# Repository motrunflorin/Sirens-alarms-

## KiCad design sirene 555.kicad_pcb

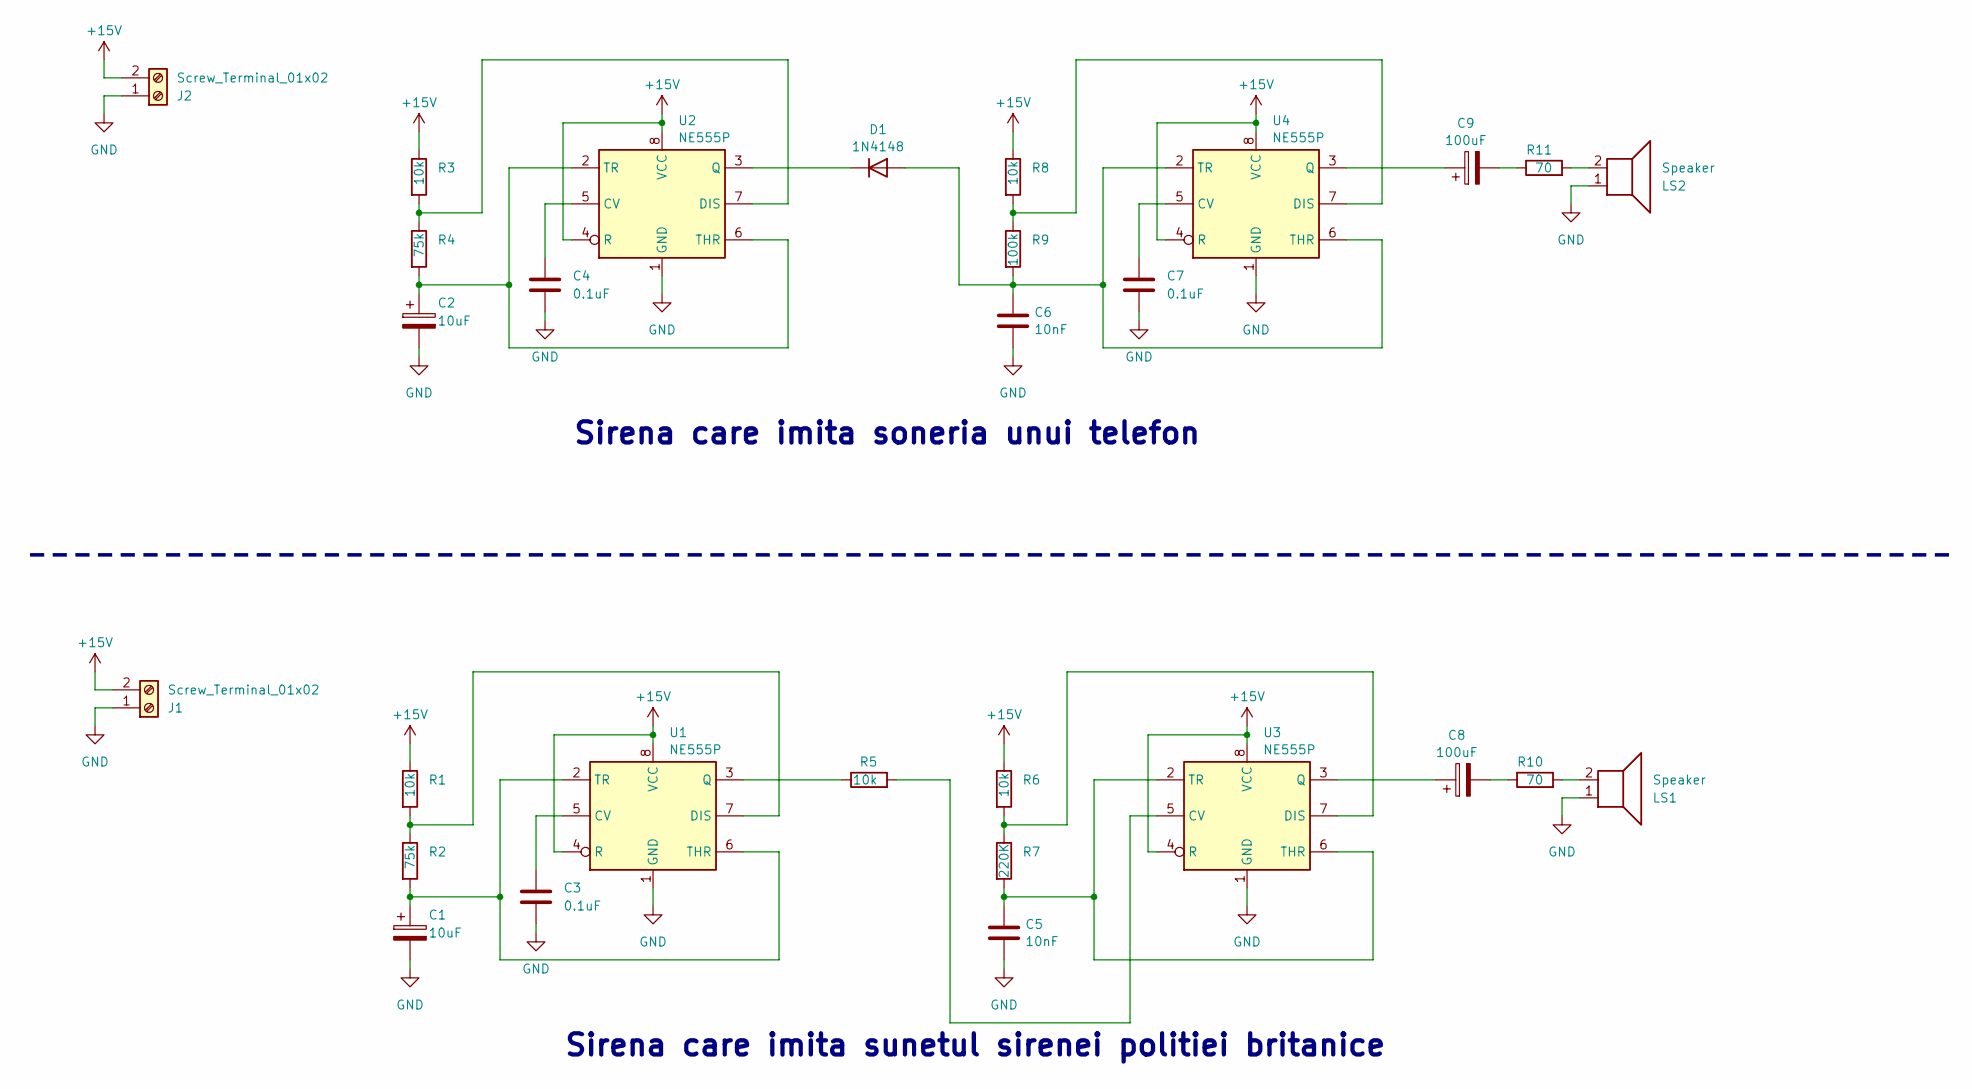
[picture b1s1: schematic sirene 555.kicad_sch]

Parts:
C1, C2: 10uF; CP_Radial_D5.0mm_P2.50mm
C3, C4, C7: 0.1uF; C_Disc_D4.3mm_W1.9mm_P5.00mm
C5, C6: 10nF; C_Disc_D4.3mm_W1.9mm_P5.00mm
C8, C9: 100uF; CP_Radial_D6.3mm_P2.50mm
D1: 1N4148; D_DO-35_SOD27_P7.62mm_Horizontal
J1, J2: Screw_Terminal_01x02; PhoenixContact_MSTBA_2,5_2-G_1x02_P5.00mm_Horizontal
LS1, LS2: Speaker; PhoenixContact_MSTBA_2,5_2-G_1x02_P5.00mm_Horizontal
R1, R3, R5, R6, R8: 10k; R_Axial_DIN0207_L6.3mm_D2.5mm_P7.62mm_Horizontal; Mfr.Part. MBB02070C1002DC100
R2, R4: 75k; R_Axial_DIN0207_L6.3mm_D2.5mm_P7.62mm_Horizontal
R7: 220K; R_Axial_DIN0207_L6.3mm_D2.5mm_P7.62mm_Horizontal
R9: 100k; R_Axial_DIN0207_L6.3mm_D2.5mm_P7.62mm_Horizontal
R10, R11: 70; R_Axial_DIN0207_L6.3mm_D2.5mm_P7.62mm_Horizontal
U1, U2, U3, U4: NE555P; DIP-8_W7.62mm

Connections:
+15V: J1.2, J2.2, R1.1, R3.1, R6.1, R8.1, U1.4 (R), U1.8 (VCC), U2.4 (R), U2.8 (VCC), U3.4 (R), U3.8 (VCC), U4.4 (R), U4.8 (VCC)
GND: C1.2, C2.2, C3.2, C4.2, C5.2, C6.2, C7.2, J1.1, J2.1, LS1.1, LS2.1, U1.1 (GND), U2.1 (GND), U3.1 (GND), U4.1 (GND)
unnamed: C8.2, R10.1
unnamed: C9.2, R11.1
unnamed: C6.1, D1.2 (A), R9.2, U4.2 (TR), U4.6 (THR)
unnamed: D1.1 (K), U2.3 (Q)
unnamed: LS1.2, R10.2
unnamed: LS2.2, R11.2
unnamed: C3.1, U1.5 (CV)
unnamed: R1.2, R2.1, U1.7 (DIS)
unnamed: R5.1, U1.3 (Q)
unnamed: C1.1, R2.2, U1.2 (TR), U1.6 (THR)
unnamed: C4.1, U2.5 (CV)
unnamed: R3.2, R4.1, U2.7 (DIS)
unnamed: C2.1, R4.2, U2.2 (TR), U2.6 (THR)
unnamed: R5.2, U3.5 (CV)
unnamed: R6.2, R7.1, U3.7 (DIS)
unnamed: C8.1, U3.3 (Q)
unnamed: C5.1, R7.2, U3.2 (TR), U3.6 (THR)
unnamed: C7.1, U4.5 (CV)
unnamed: R8.2, R9.1, U4.7 (DIS)
unnamed: C9.1, U4.3 (Q)

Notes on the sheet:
Sirena care imita sunetul sirenei politiei britanice
Sirena care imita soneria unui telefon

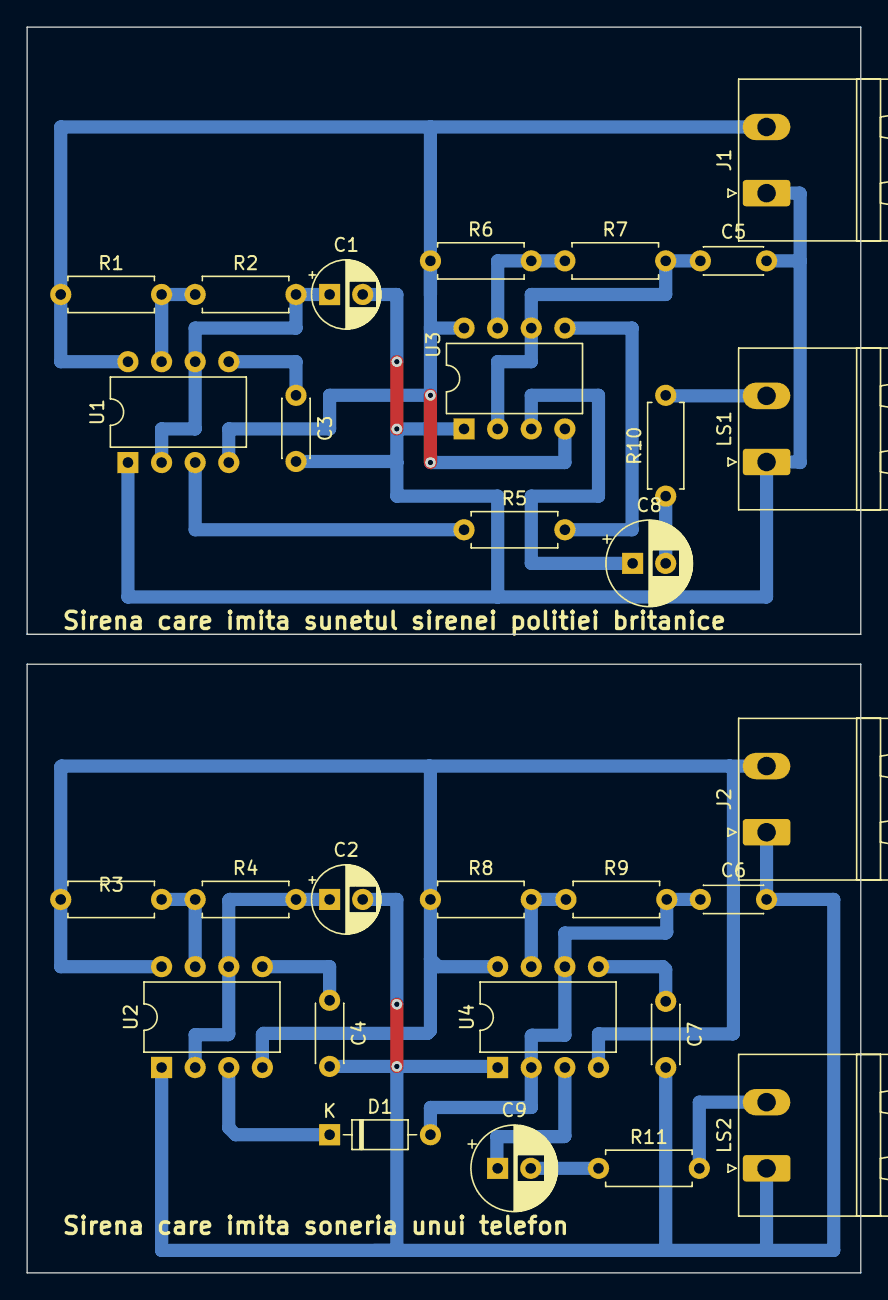
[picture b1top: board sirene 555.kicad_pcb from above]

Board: 2 copper layers, 63.0 x 94.1 mm, 29 parts (0 on the bottom side), 22 nets.
